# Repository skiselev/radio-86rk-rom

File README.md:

# Radio 86RK - ROM Cartridge
ROM cartridge for my [Radio-86RK](https://github.com/skiselev/radio-86rk) implementation

## Introduction
This ROM cartridge provides 16 KiB - 32 KiB ROM, that can be used to store the software - development tools, games, and so on.
The ROM cartridge connects to Radio-86RK using the 8255 PPI based parallel interface.

## Using ROM Cartridge

Make sure to power off the computer before connecting the cartridge. Connect the cartridge to the computer using a 26 conductor flat ribbon cable. 

The Radio-86RK ROM monitor provides [**R** command](https://github.com/skiselev/radio-86rk#monitor) that can be used to copy of the ROM cartridge to computer's RAM.
The syntax of **R** command is:
**R\<ROM_Start_Address\>,\<ROM_End_Address\>,\<Destination_Start_Address\>**

The ROM monitor also provides a subroutine to copy ROM cartridge content to the RAM:

* Entry point: 0FA68H
* Input registers:
  * HL - ROM start address
  * DE - ROM end address
  * BC - RAM start address

## Hardware Documentation

### Schematic and PCB Layout

[Schematic - Version 1.1](KiCad/radio-86rk-rom-Schematic-1.1.pdf)

[PCB Layout - Version 1.1](KiCad/radio-86rk-rom-Board-1.1.pdf)

### Connectors and Jumpers

#### J1 - Parallel Port Connector
Pin | Description | Pin | Description
--- | ----------- | --- | ----------------
1   | Output: A8  | 2   | Output: D0
3   | Output: A9  | 4   | Output: D1
5   | Output: A10 | 6   | Output: D2
7   | Output: A11 | 8   | Output: D3
9   | Output: A12 | 10  | Output: D4
11  | Output: A13 | 12  | Output: D5
13  | Output: A14 | 14  | Output: D6
15  | Output: /ROM_CE | 16  | Output: D7
17  | Output: A7 | 18  | Input: A0
19  | Output: A6 | 20  | Input: A1
21  | Output: A5 | 22  | Input: A2
23  | Output: A4 | 24  | Input: A3
25  | Power: +5V  | 26  | Power: GND

#### JP1 and JP2 - ROM Type Configuration

JP1 determines the connection of the ROM's pin 1, while JP2 determines the connection of the ROM's pin 27

ROM Type       | Jumper 1 Position      | Jumper 2 Position
-------------- | ---------------------- | ----------------------------
27C128         | JP1 - 2-3              | JP2 - 1-2 (jumper installed)
27C256, 29C256 | JP1 pin 1 to JP2 pin 1 | JP1 pin 2 to JP2 pin 2
28C256, NVRAM  | JP1 - 1-2              | JP2 - 1-2 (jumper installed)

### Bill of Materials

* [Radio-86RK-ROM project on Mouser.com](https://www.mouser.com/ProjectManager/ProjectDetail.aspx?AccessID=xxxxxxxxxx) - View and order all component except of the PCB.

* [Unicorn Electronics](https://www.unicornelectronics.com/prod.htm) is a good source for UV ERPROMs and EEPROMs

Component type     | Reference | Description                                 | Quantity | Possible sources and notes
------------------ | --------- | ------------------------------------------- | -------- | --------------------------
PCB                |           | Radio-86RK ROM Cartridge PCB - Version 1.1  | 1        | Buy from my Tindie store: [Radio-86RK - PCB](https://www.tindie.com/products/weird/radio-86rk-pcb/) or order from a PCB manufacturer of your choice using provided Gerber or KiCad files
Capacitor          | C1        | 0.1 uF, MLCC, 5 mm Pitch                    | 1        | Mouser [594-K104K15X7RF53H5](https://www.mouser.com/ProductDetail/594-K104K15X7RF53H5)
Connector          | J1        | 13x2 pin header, shrouded                   | 1        | Mouser [517-30326-6002](https://www.mouser.com/ProductDetail/517-30326-6002)
Connector          | JP1       | 3 pin header                                | 1        | Mouser [855-M20-9990345](https://www.mouser.com/ProductDetail/855-M20-9990345)
Connector          | JP2       | 2 pin header                                | 1        | Mouser [855-M20-9990245](https://www.mouser.com/ProductDetail/855-M20-9990245)
Integrated Circuit | U1        | 28C256, 27C256, 27C128                      | 1        | Unicorn Electronics [27C256, 27C128](https://www.unicornelectronics.com/IC/EPROM.html), [28C256](https://www.unicornelectronics.com/IC/EEPROM.html), Mouser [556-AT28C25615PU](https://www.mouser.com/ProductDetail/556-AT28C25615PU)
IC Socket          | U1        | 28 pin DIP                                  | 1        | Mouser [649-DILB28P223TLF](https://www.mouser.com/ProductDetail/649-DILB28P223TLF), [517-4828-6000-CP](https://www.mouser.com/ProductDetail/517-4828-6000-CP)
Connector          | Cable Assembly | 13x2 pin IDC socket                    | 2        | Mouser [517-D89126-0131HK](https://www.mouser.com/ProductDetail/517-D89126-0131HK)
Cable              | Cable Assembly | 26 conductor flat ribbon cable, 1 ft.  | 1        | Mouser [517-3365/26FT](https://www.mouser.com/ProductDetail/517-3365-26FT)

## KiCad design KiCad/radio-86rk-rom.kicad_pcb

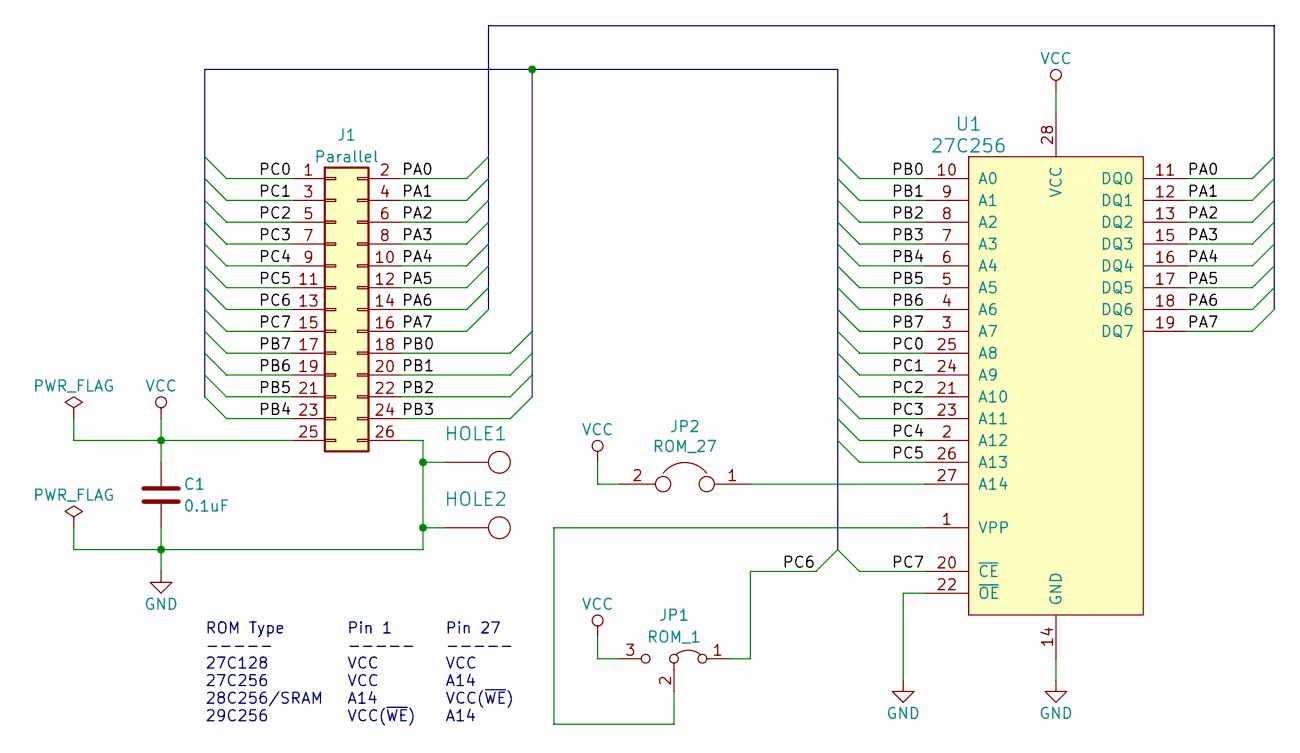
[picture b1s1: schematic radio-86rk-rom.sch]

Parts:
C1: 0.1uF; Cap_Cer_508
HOLE1, HOLE2: HOLE; Hole_3mm
J1: Parallel; Conn_Pin_Header_13x2_2.54mm_Shrouded
JP1: ROM_1; Conn_Pin_Header_3x1_2.54mm
JP2: ROM_27; Conn_Pin_Header_2x1_2.54mm
U1: 27C256; IC_DIP28_600

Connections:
/PA0: J1.2, U1.11 (DQ0)
/PA1: J1.4, U1.12 (DQ1)
/PA2: J1.6, U1.13 (DQ2)
/PA3: J1.8, U1.15 (DQ3)
/PA4: J1.10, U1.16 (DQ4)
/PA5: J1.12, U1.17 (DQ5)
/PA6: J1.14, U1.18 (DQ6)
/PA7: J1.16, U1.19 (DQ7)
/PB0: J1.18, U1.10 (A0)
/PB1: J1.20, U1.9 (A1)
/PB2: J1.22, U1.8 (A2)
/PB3: J1.24, U1.7 (A3)
/PB4: J1.23, U1.6 (A4)
/PB5: J1.21, U1.5 (A5)
/PB6: J1.19, U1.4 (A6)
/PB7: J1.17, U1.3 (A7)
/PC0: J1.1, U1.25 (A8)
/PC1: J1.3, U1.24 (A9)
/PC2: J1.5, U1.21 (A10)
/PC3: J1.7, U1.23 (A11)
/PC4: J1.9, U1.2 (A12)
/PC5: J1.11, U1.26 (A13)
/PC6: J1.13, JP1.1 (A)
/PC7: J1.15, U1.20 (~CE)
GND: C1.2, HOLE1.1, HOLE2.1, J1.26, U1.14 (GND), U1.22 (~OE)
unnamed: JP1.2 (C), U1.1 (VPP)
unnamed: JP2.1, U1.27 (A14)
VCC: C1.1, J1.25, JP1.3 (B), JP2.2, U1.28 (VCC)

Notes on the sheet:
ROM Type ----- 27C128 27C256 28C256/SRAM 29C256
Pin 1 ----- VCC VCC A14 VCC(~WE~)
Pin 27 ----- VCC A14 VCC(~WE~) A14

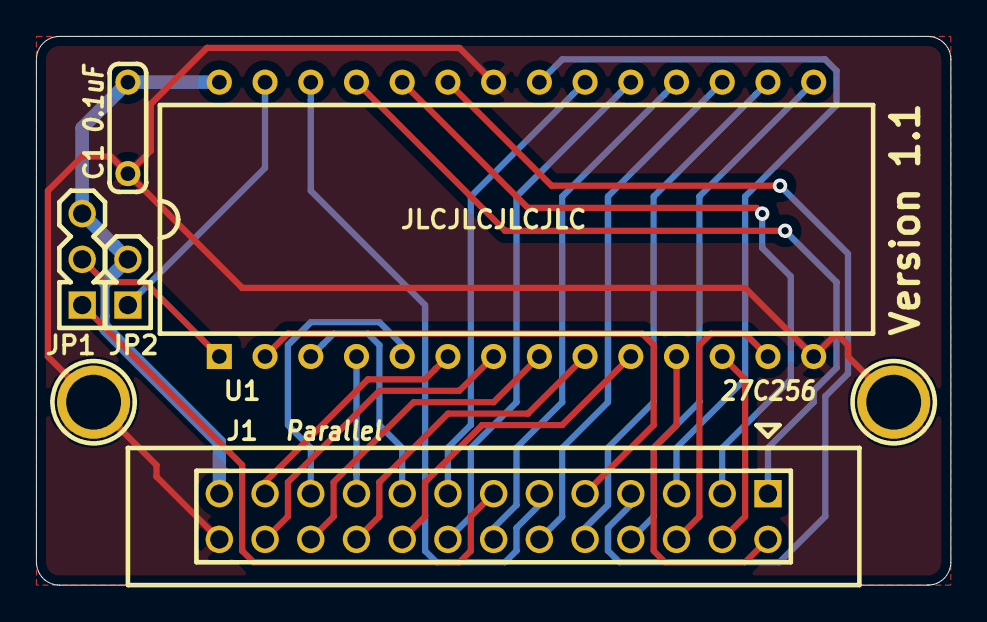
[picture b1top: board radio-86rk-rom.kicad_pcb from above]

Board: 2 copper layers, 50.8 x 30.5 mm, 7 parts (0 on the bottom side), 28 nets.

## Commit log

2020-02-28 Populate KiCad and Gerber files

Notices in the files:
KiCad/radio-86rk-rom.kicad_pcb:
GPL
Copyright (C) 2020 Sergey Kiselev
